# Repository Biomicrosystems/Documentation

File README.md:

# Logos
- The Logo of our group, and all of its versions, has been developed by Designer and Electronic Engineer Gina Paola Salazar

# Figures for papers, presentations, thesis and posters
- All figures of equipment and microsystems were produced by Designer Maria Alejandra Mariño 

When using these images please acknowledge respectively

# File Formats
- LABBOOK: The Excel file format of our groups to document your experimental data
- Confidential Agreement (NDA): document to sign the confidential agreement of the group (spanish version)
- Poster: Our group's powerpoint format for posters
- Presentation: Our group's powerpoint format for presentations

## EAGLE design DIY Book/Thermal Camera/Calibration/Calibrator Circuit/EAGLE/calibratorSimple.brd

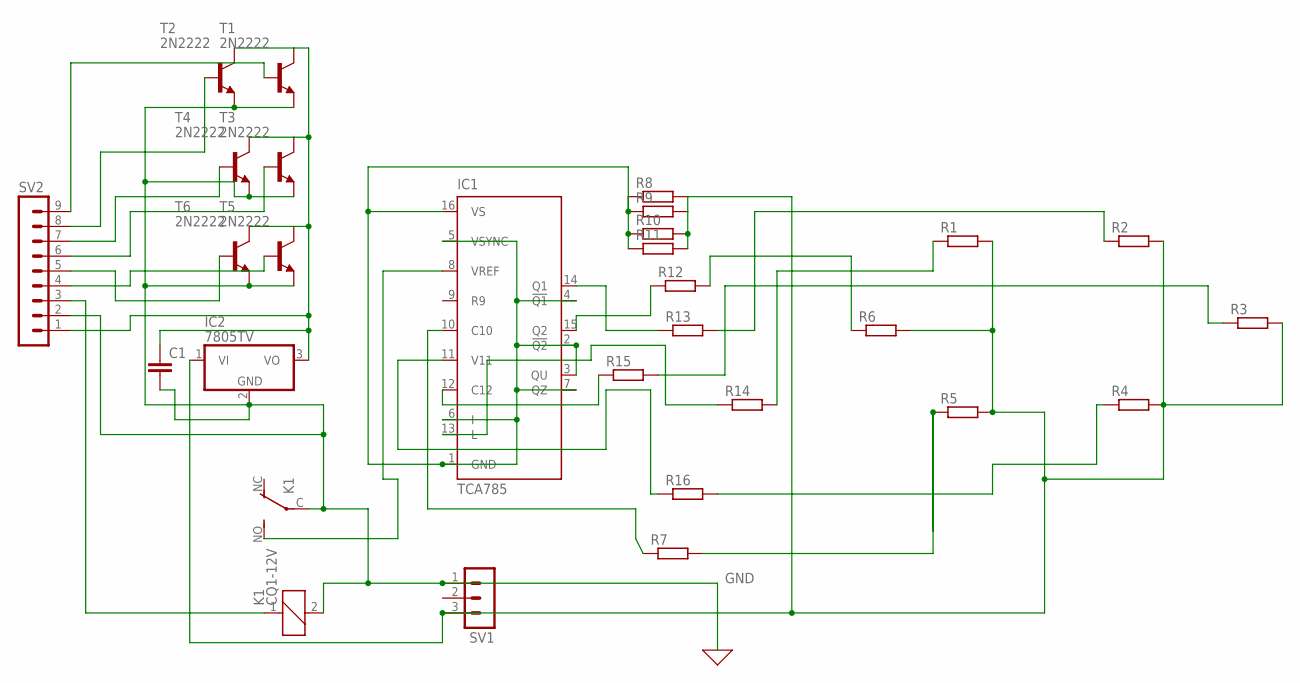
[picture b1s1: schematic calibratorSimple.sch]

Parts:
C1: C2.5/2; C2.5-2
IC1: TCA785; DIL16
IC2: 7805TV; TO220V
K1: CQ1-12V; CQ1
R1, R2, R3, R4, R5, R6: R-EU_0207/15; 0207/15
R7, R8, R9, R10, R11, R12, R13, R14, R15, R16: R-EU_0204/7; 0204/7
SV1: MA03-1
SV2: MA09-1
T1, T2, T3, T4, T5, T6: 2N2222; TO18

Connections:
GND: C1.2, IC2.2 (GND), K1.2, K1.C, SV1.1, SV2.2, T1.1 (E), T2.1 (E), T3.1 (E), T4.1 (E), T5.1 (E), T6.1 (E)
unnamed: IC1.11 (V11), R16.1
unnamed: IC2.1 (VI), R1.2, R2.2, R3.2, R4.2, R5.2, R6.2, R8.2, R9.2, R10.2, R11.2, SV1.3
unnamed: R1.1, R14.2
unnamed: R4.1, R16.2
unnamed: R3.1, R15.2
unnamed: R6.1, R12.2
unnamed: R5.1, R7.2
unnamed: R2.1, R13.2
unnamed: IC1.1 (GND), IC1.2 (!Q2), IC1.3 (QU), IC1.4 (!Q1), IC1.5 (VSYNC), IC1.6 (I), IC1.7 (QZ), IC1.16 (VS), R8.1, R9.1, R10.1, R11.1
unnamed: IC1.15 (Q2), R12.1
unnamed: IC1.12 (C12), R15.1
unnamed: IC1.14 (Q1), R13.1
unnamed: IC1.13 (L), R14.1
unnamed: IC1.8 (VREF), K1.NO (S)
unnamed: IC1.10 (C10), R7.1
unnamed: SV2.4, T5.2 (B)
unnamed: C1.1, IC2.3 (VO), SV2.1, T1.3 (C), T2.3 (C), T3.3 (C), T4.3 (C), T5.3 (C), T6.3 (C)
unnamed: K1.1, SV2.3
unnamed: SV2.5, T6.2 (B)
unnamed: SV2.6, T3.2 (B)
unnamed: SV2.7, T4.2 (B)
unnamed: SV2.8, T2.2 (B)
unnamed: SV2.9, T1.2 (B)

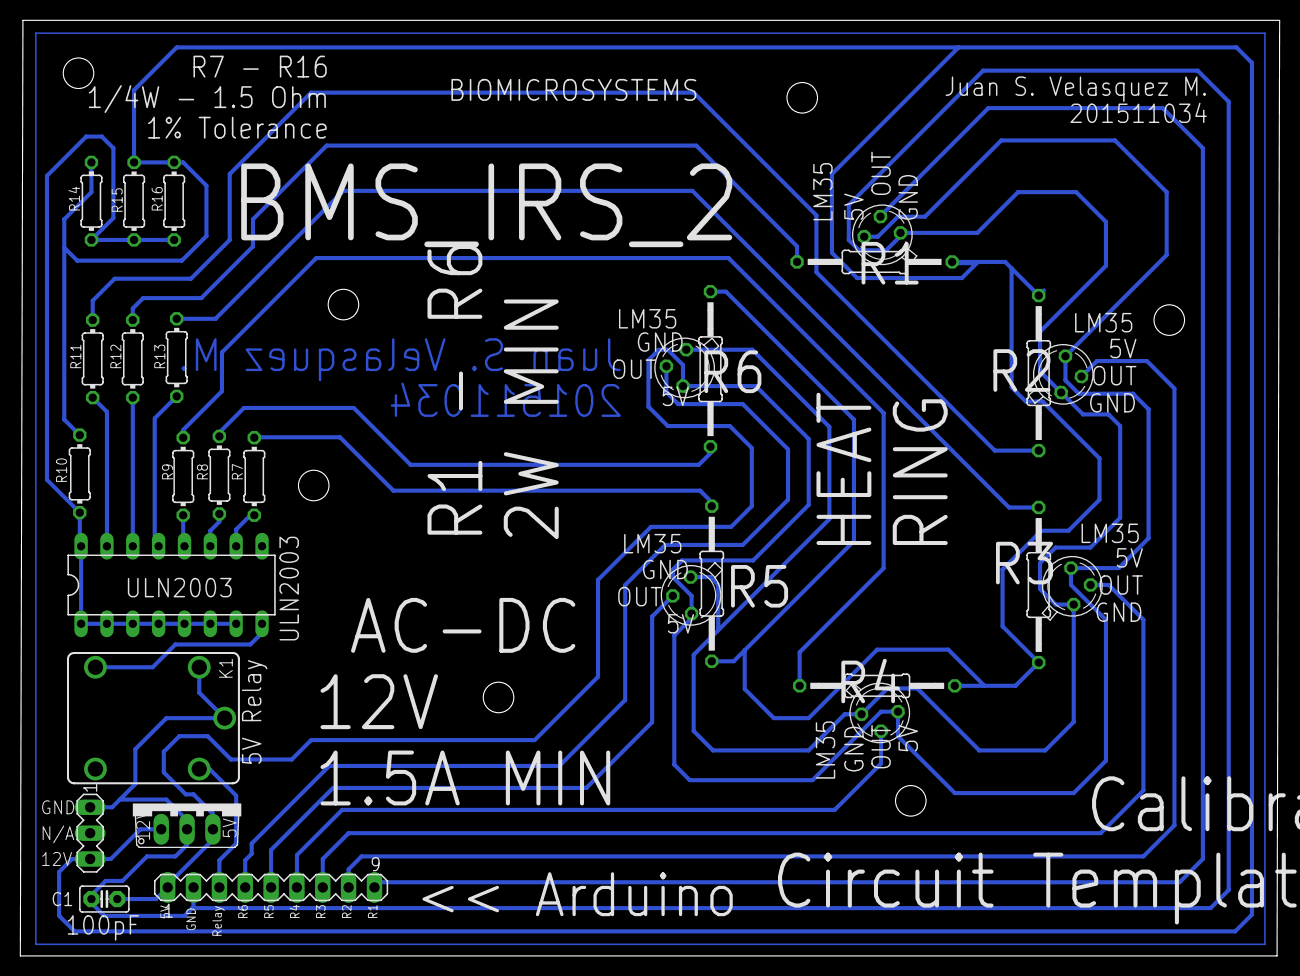
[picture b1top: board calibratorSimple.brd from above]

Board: 2 copper layers, 123.7 x 91.9 mm, 28 parts (0 on the bottom side), 24 nets.

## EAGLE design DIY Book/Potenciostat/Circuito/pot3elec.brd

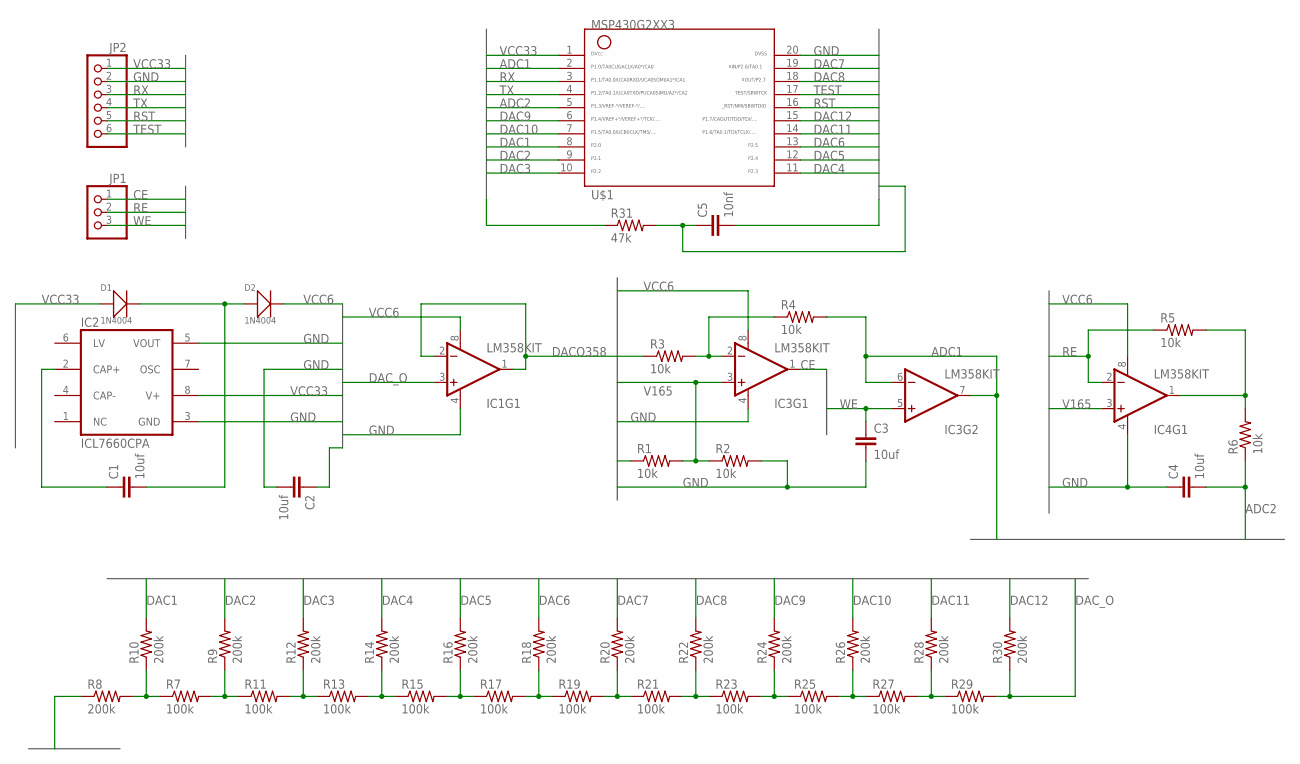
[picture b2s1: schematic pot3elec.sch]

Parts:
C1, C2, C3, C4: 10uf; C2.5-3
C5: 10nf; C2.5-3
D1, D2: 1N4004; DO-41
IC1, IC3, IC4: LM358KIT; DIP08-KIT
IC2: ICL7660CPA; DIL08
JP1: PINHD-1X3; 1X03
JP2: PINHD-1X6; 1X06
R1, R2, R3, R4, R5, R6: 10k; 1206
R7, R11, R13, R15, R17, R19, R21, R23, R25, R27, R29: 100k; 1206
R8, R9, R10, R12, R14, R16, R18, R20, R22, R24, R26, R28, R30: 200k; 1206
R31: 47k; 1206
U$1: G2XX3---N20; N20

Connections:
ADC1: IC3.6 (-IN), IC3.7 (OUT), R4.2, U$1.2
ADC2: C4.2, R6.1, U$1.5
CE: IC3.1 (OUT), JP1.1
DAC1: R10.2, U$1.8
DAC2: R9.2, U$1.9
DAC3: R12.2, U$1.10
DAC4: R14.2, U$1.11
DAC5: R16.2, U$1.12
DAC6: R18.2, U$1.13
DAC7: R20.2, U$1.19
DAC8: R22.2, U$1.18
DAC9: R24.2, U$1.6
DAC10: R26.2, U$1.7
DAC11: R28.2, U$1.14
DAC12: R30.2, U$1.15
DACO358: IC1.1 (OUT), IC1.2 (-IN), R3.1
DAC_O: IC1.3 (+IN), R29.2, R30.1
GND: C2.2, C3.2, C4.1, C5.2, IC1.4 (V-), IC2.3 (GND), IC2.5 (VOUT), IC3.4 (V-), IC4.4 (V-), JP2.2, R2.2, R8.1, U$1.20
unnamed: C1.2, D1.2 (-), D2.1 (+)
unnamed: C1.1, IC2.2 (CAP+)
unnamed: IC4.1 (OUT), R5.2, R6.2
unnamed: IC3.2 (-IN), R3.2, R4.1
unnamed: R7.1, R8.2, R10.1
unnamed: R7.2, R9.1, R11.1
unnamed: R11.2, R12.1, R13.1
unnamed: R13.2, R14.1, R15.1
unnamed: R15.2, R16.1, R17.1
unnamed: R17.2, R18.1, R19.1
unnamed: R19.2, R20.1, R21.1
unnamed: R21.2, R22.1, R23.1
unnamed: R23.2, R24.1, R25.1
unnamed: R25.2, R26.1, R27.1
unnamed: R27.2, R28.1, R29.1
RE: IC4.2 (-IN), JP1.2, R5.1
RST: C5.1, JP2.5, R31.2, U$1.16
RX: JP2.3, U$1.3
TEST: JP2.6, U$1.17
TX: JP2.4, U$1.4
V165: IC3.3 (+IN), IC4.3 (+IN), R1.2, R2.1
VCC6: C2.1, D2.2 (-), IC1.8 (V+), IC3.8 (V+), IC4.8 (V+)
VCC33: D1.1 (+), IC2.8 (V+), JP2.1, R1.1, R31.1, U$1.1
WE: C3.1, IC3.5 (+IN), JP1.3

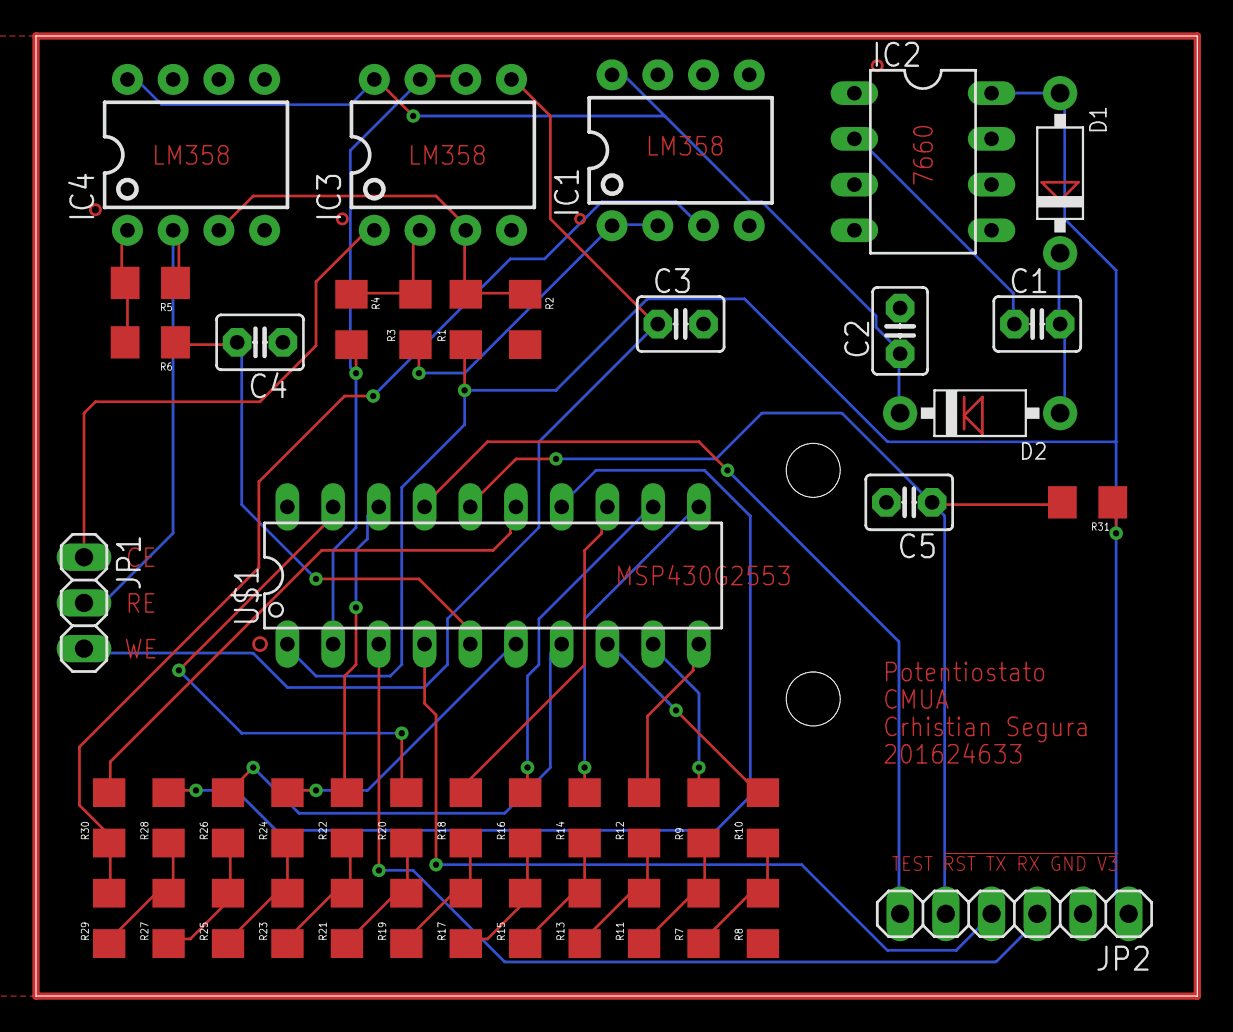
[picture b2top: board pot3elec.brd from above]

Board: 2 copper layers, 64.5 x 53.3 mm, 45 parts (0 on the bottom side), 42 nets.

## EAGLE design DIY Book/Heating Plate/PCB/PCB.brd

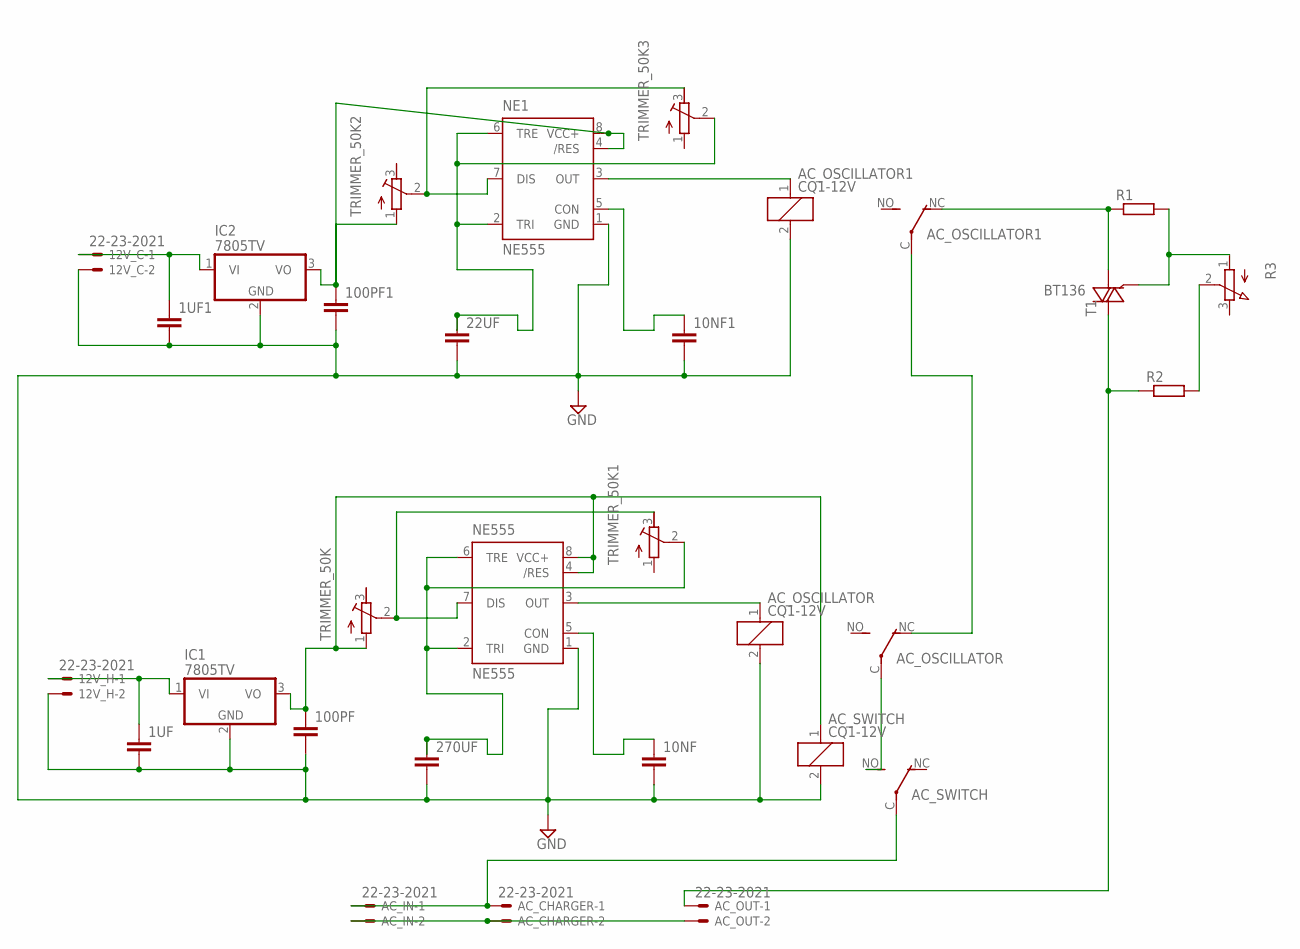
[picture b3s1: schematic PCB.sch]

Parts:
1UF, 1UF1, 10NF, 10NF1, 22UF, 100PF, 100PF1, 270UF: C7.5/3; C7.5B3
12V_C, 12V_H: 22-23-2021
AC_CHARGER: 22-23-2021
AC_IN: 22-23-2021
AC_OSCILLATOR, AC_OSCILLATOR1: CQ1-12V; CQ1
AC_OUT: 22-23-2021
AC_SWITCH: CQ1-12V; CQ1
IC1, IC2: 7805TV; TO220V
NE1, NE555: NE555; DIL-08
R1, R2: R-EU_0204/7; 0204/7
R3: 3RP/1610N
T1: BT136; TO220AB
TRIMMER_50K, TRIMMER_50K1, TRIMMER_50K2, TRIMMER_50K3: R-TRIMM64W; RTRIM64W

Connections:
GND: 1UF.2, 1UF1.2, 10NF.2, 10NF1.2, 12V_C.2, 12V_H.2, 22UF.2, 100PF.2, 100PF1.2, 270UF.2, AC_OSCILLATOR.2, AC_OSCILLATOR1.2, AC_SWITCH.2, IC1.2 (GND), IC2.2 (GND), NE1.1 (GND), NE555.1 (GND)
unnamed: AC_CHARGER.1, AC_IN.1, AC_SWITCH.C
unnamed: AC_CHARGER.2, AC_IN.2, AC_OUT.2
unnamed: 10NF1.1, NE1.5 (CON)
unnamed: AC_OSCILLATOR.1, NE555.3 (OUT)
unnamed: 10NF.1, NE555.5 (CON)
unnamed: NE555.7 (DIS), TRIMMER_50K.2 (S), TRIMMER_50K1.3 (E)
unnamed: AC_OSCILLATOR.C, AC_SWITCH.NO (S)
unnamed: AC_OSCILLATOR.NC (O), AC_OSCILLATOR1.C
unnamed: 1UF.1, 12V_H.1, IC1.1 (VI)
unnamed: 270UF.1, NE555.2 (TRI), NE555.6 (TRE), TRIMMER_50K1.2 (S)
unnamed: R1.2, R3.1 (A), T1.3 (G)
unnamed: AC_OSCILLATOR1.NC (O), R1.1, T1.1 (A1)
unnamed: 100PF.1, AC_SWITCH.1, IC1.3 (VO), NE555.4 (/RES), NE555.8 (VCC+), TRIMMER_50K.1 (A)
unnamed: 22UF.1, NE1.2 (TRI), NE1.6 (TRE), TRIMMER_50K3.2 (S)
unnamed: NE1.7 (DIS), TRIMMER_50K2.2 (S), TRIMMER_50K3.3 (E)
unnamed: AC_OSCILLATOR1.1, NE1.3 (OUT)
unnamed: R2.2, R3.2 (S)
unnamed: 1UF1.1, 12V_C.1, IC2.1 (VI)
unnamed: AC_OUT.1, R2.1, T1.2 (A2)
unnamed: 100PF1.1, IC2.3 (VO), NE1.4 (/RES), NE1.8 (VCC+), TRIMMER_50K2.1 (A)

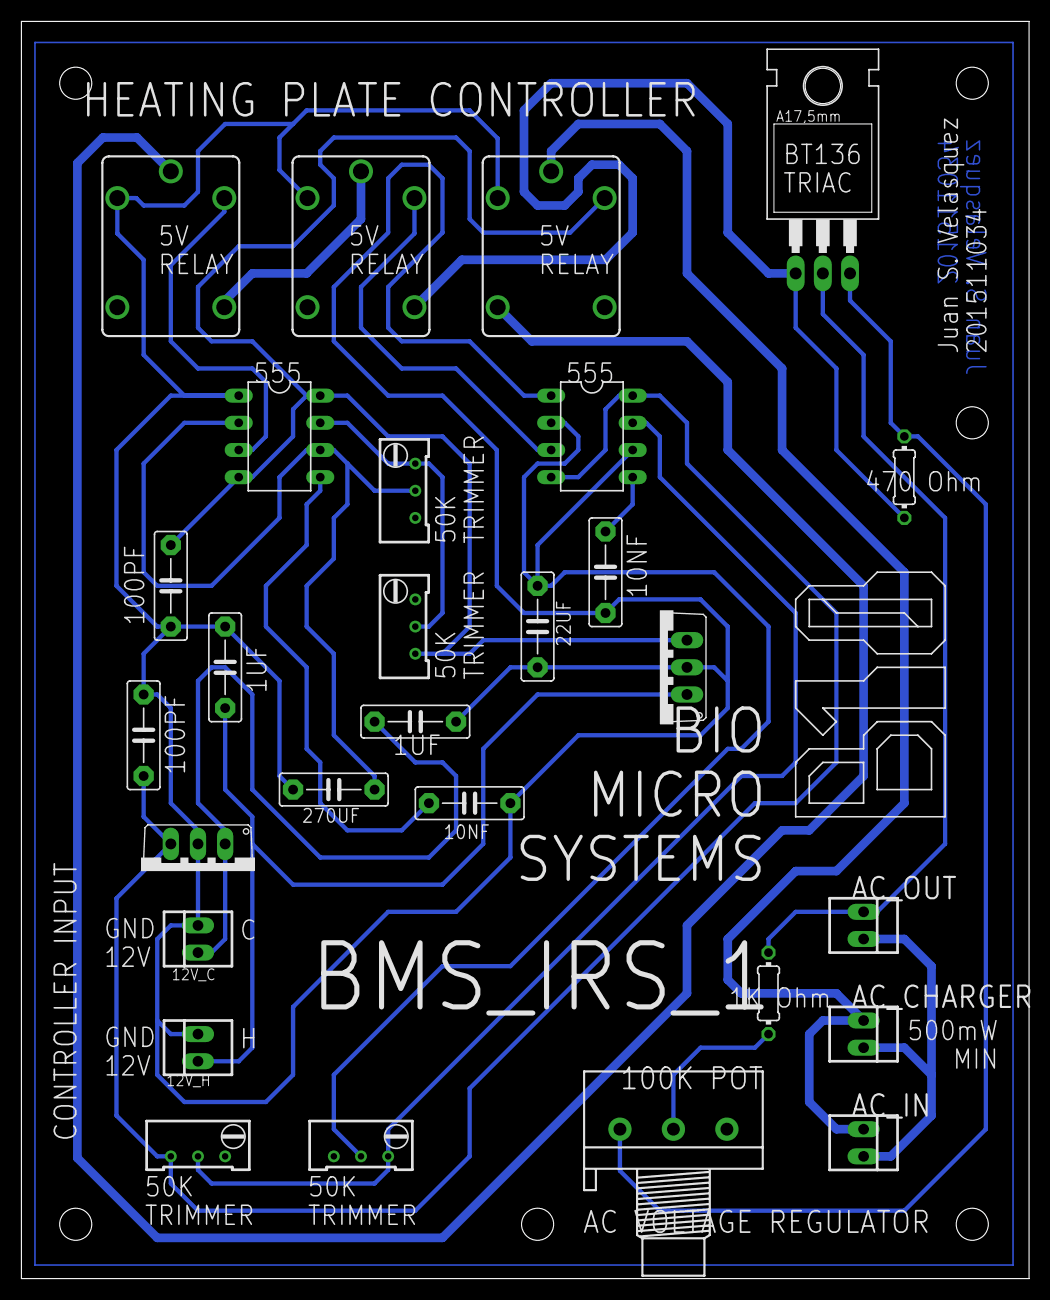
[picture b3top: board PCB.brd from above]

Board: 2 copper layers, 94.2 x 117.5 mm, 28 parts (0 on the bottom side), 21 nets.

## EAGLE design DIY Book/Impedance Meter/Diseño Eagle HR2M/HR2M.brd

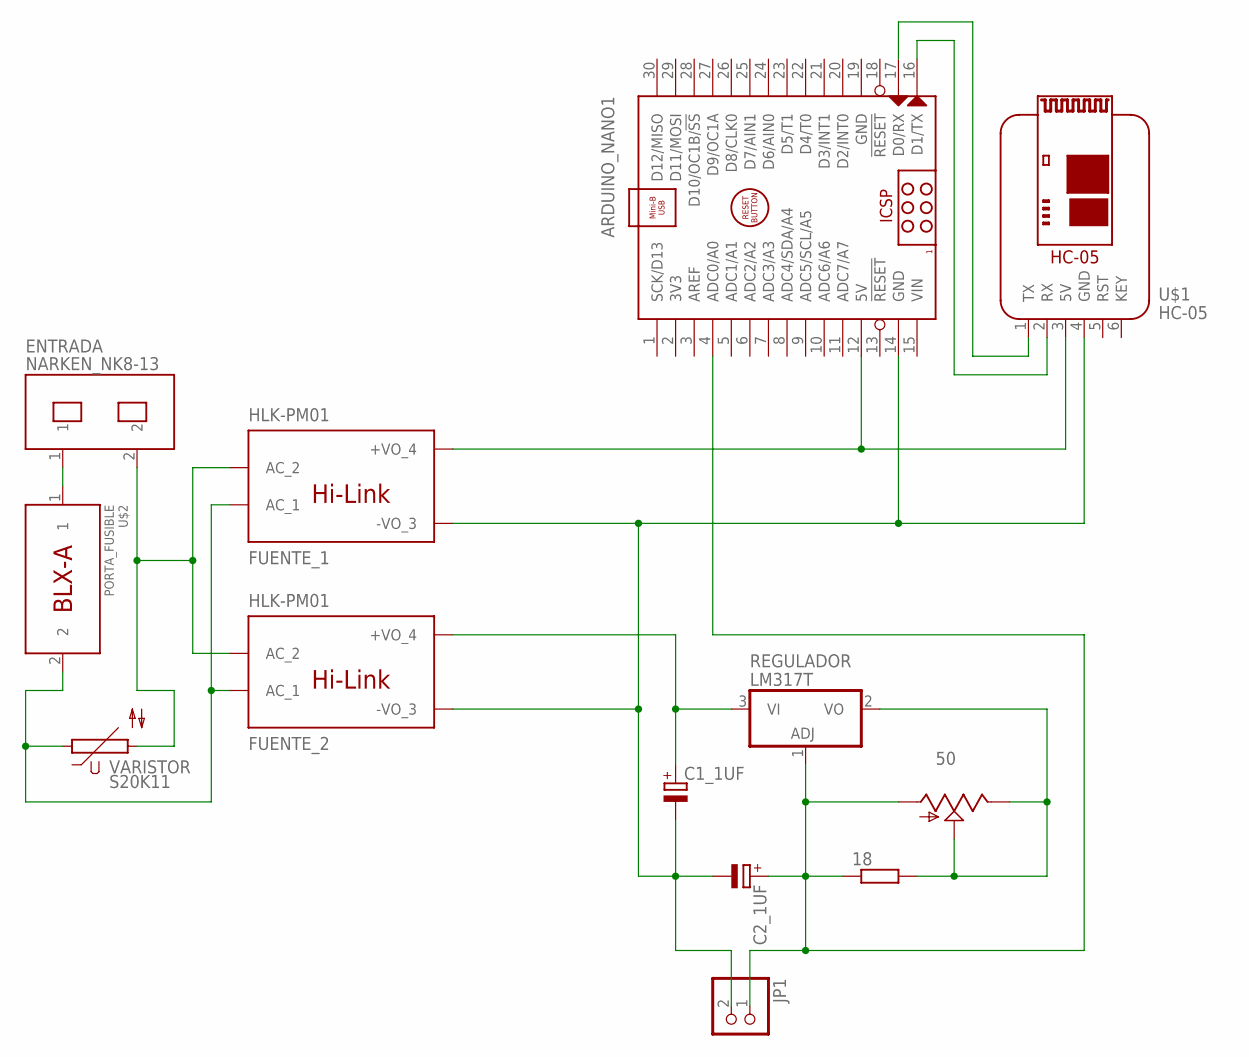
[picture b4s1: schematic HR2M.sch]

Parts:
18: R-EU_0207/12; 0207/12
50: TRIM_US-B64Y; B64Y
ARDUINO_NANO1: ARDUINO_NANO
C1_1UF, C2_1UF: CPOL-EUE2.5-6; E2,5-6
ENTRADA: NARKEN_NK8-13
FUENTE_1, FUENTE_2: HLK-PM01
JP1: PINHD-1X2; 1X02
REGULADOR: LM317T; TO220V
U$1: HC-05; HC-0X_V
U$2: PORTA_FUSIBLE
VARISTOR: S20K11

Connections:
GND: ARDUINO_NANO1.14 (GND), ARDUINO_NANO1.19 (GND), C1_1UF.-, C2_1UF.-, FUENTE_1.-VO_3, FUENTE_2.-VO_3, JP1.2, U$1.4 (GND)
unnamed: ENTRADA.1, U$2.1
unnamed: ARDUINO_NANO1.12 (5V), FUENTE_1.+VO_4, U$1.3 (5V)
unnamed: ENTRADA.2, FUENTE_1.AC_2, FUENTE_2.AC_2, VARISTOR.2
unnamed: ARDUINO_NANO1.17 (D0/RX), U$1.1 (TX)
unnamed: FUENTE_1.AC_1, FUENTE_2.AC_1, U$2.2, VARISTOR.1
unnamed: ARDUINO_NANO1.16 (D1/TX), U$1.2 (RX)
unnamed: C1_1UF.+, FUENTE_2.+VO_4, REGULADOR.3 (VI)
unnamed: 18.1, 50.A, ARDUINO_NANO1.4 (ADC0/A0), C2_1UF.+, JP1.1, REGULADOR.1 (ADJ)
unnamed: 18.2, 50.E, 50.S, REGULADOR.2 (VO)
VIN: ARDUINO_NANO1.15 (VIN)

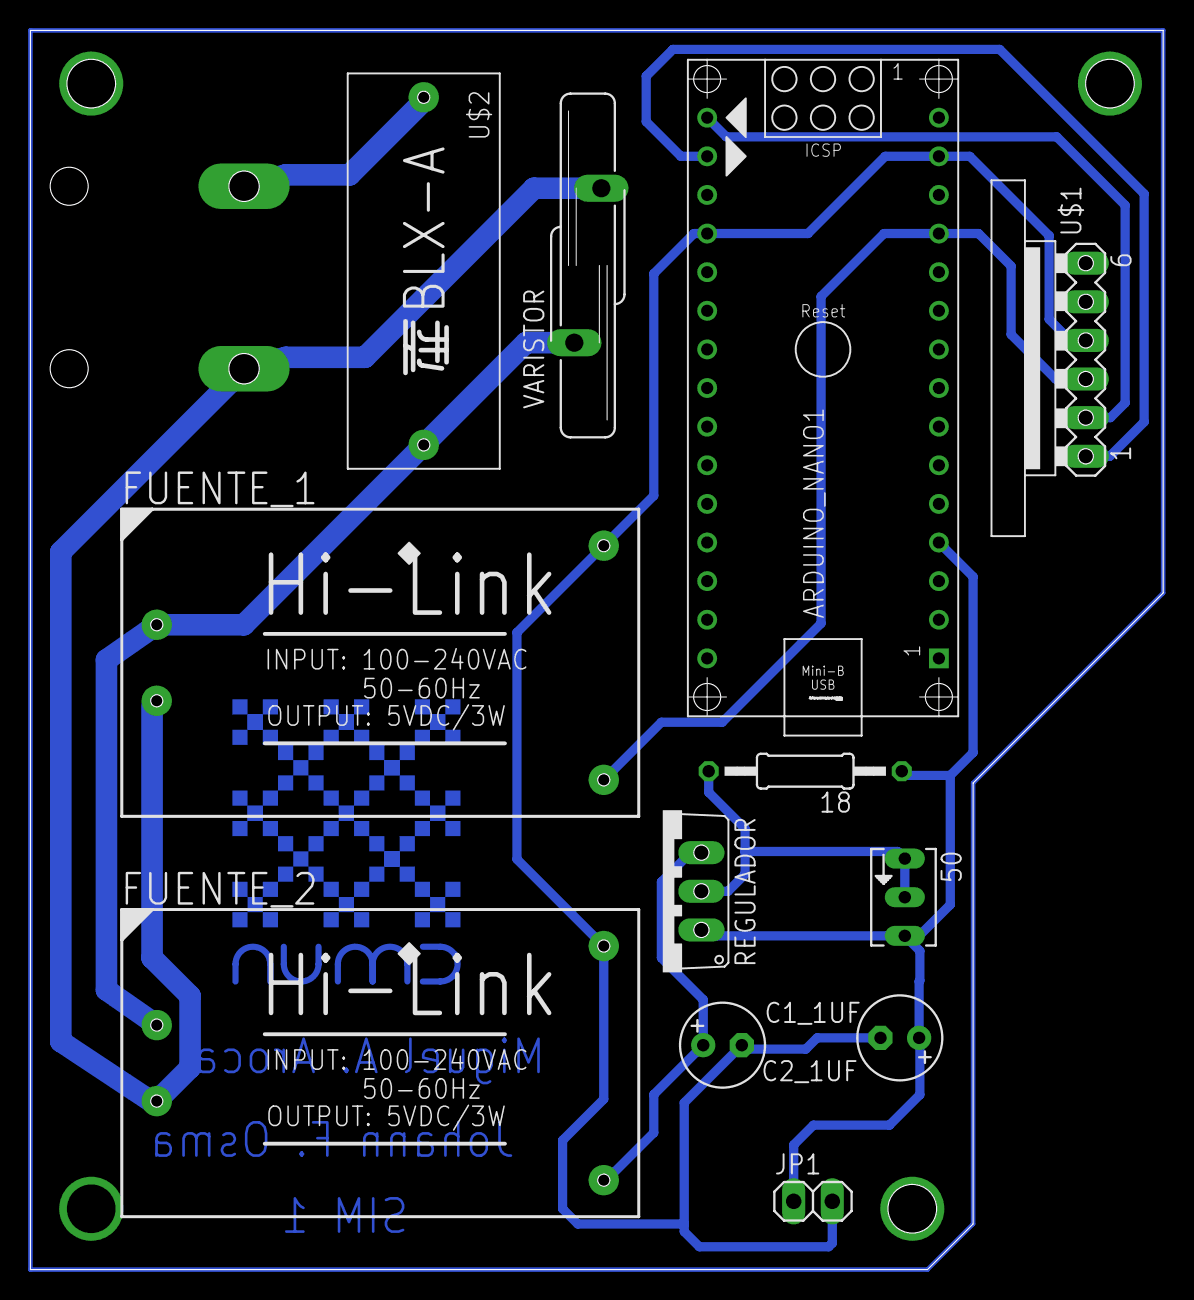
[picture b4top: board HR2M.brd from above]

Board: 2 copper layers, 74.5 x 81.5 mm, 13 parts (1 on the bottom side), 10 nets.

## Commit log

2022-04-19 add VS gitignore
2022-04-19 invert current value
2022-04-28 Add config json
2022-04-28 Update executable files
2022-08-20 Upgrade Installer to V 1.1.0.0
2022-08-20 Update latest pc version
    Latest Pc software is updated
2022-09-16 Documentacion uso y manejo del potenciostato
2023-01-19 Create adsfads
2023-01-19 Rename Videos.md to README.md
2023-02-01 Create gitkeep
2023-02-19 Create: Folder photos principal page biomicrosystems
2023-02-19 Update: Update photos - page biomicrosystems
2023-02-19 Update Update photos
2023-03-02 Page-web
2023-03-05 Feature: photo page areas
2023-03-05 Feature: Delete file in proyect
2023-03-05 Feature: Add proeyct in angular, pricnipal proyect
2023-03-05 Feature: Ajust logic members & styles
2023-03-06 Features: Added member cards
2023-03-16 Added Individual Photos
2023-03-16 Features: Added Members
2023-03-17 Feature: Added all I&M members
2023-03-17 Feature: Added Members to RSA
2023-03-18 Feature: Classified unassigned members
2023-03-19 Feature: Adjust button member page & navbar component
2023-03-19 Feature: Update publications page
2023-03-19 Feature: Update member Page
2023-03-19 Feature: Adjust size individual photos
2023-03-22 Added member pictures
2023-03-22 Feature: Corrections in members page
2023-03-22 Feature: Added missing active members
2023-03-23 Feature: Added members' missing information
2023-04-06 Feature: Clear Code
2023-04-06 Featute: Create carousel
2023-04-06 Feature: Folder carousel photos
2023-04-06 Feature: Adjust Carousel
2023-04-12 Feature: Added ALL pending graduate members
2023-04-12 Fixed cards with missing info
2023-04-13 Feature: Adjust responsive page
2023-04-13 Feature: Adjust responsive footer
2023-04-14 Arreglos página
2023-04-14 Feature: minor corrections
2023-04-17 PAWL-CLIENT
    Aqui se encontrará el código fuente con el que debe ser programado el microcontrolador
2023-04-17 PAWL-UI
    Aquí se muestra la interfaz gradica de PAWL
2023-04-17 PAWL-UI
    Aquí se muestra el código relacionado con la API del sistema
2023-04-27 Feature: Uodate carousel in principal-page
2023-06-26 Feature: Update page
2023-06-26 Update: Update page biomicrosuystem
2023-06-26 Update: delete comment
2023-06-26 Feature: Adjust styles footer
2023-06-26 Feature: Adjust page
2023-06-26 Feature: Fixed members photos and footer grammar
2023-06-27 Feature: Update footer & index, in page.
2023-06-29 Feature: Files dockerization image project
2023-07-06 Add files via upload
    Este archivo presenta la versión final del programa de arduino IDE para controlar el robot a través de un microcontrolador Nodemcu basado en ESP8266.
2024-01-29 Bomba jeringa para microfluidica
2024-09-24 Documentacíon CBU IronMan
2024-09-25 IRON APK

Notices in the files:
parts and their libraries:
SparkFun-AnalogIC: Licensing:Creative Commons ShareAlike 4.0 International - https://creativecommons.org/licenses/by-sa/4.0
